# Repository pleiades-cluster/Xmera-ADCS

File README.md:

# Xmera-ADCS
The Official ADCS Design on PROVES Xmera
# ADCS_V1
This was the first version of the ADCS board developed by Rachel Sarmiento and Nicole Maggard. This board was uploaded on 10/12/2022 and is the most relevant and up to date version. This board utilizes a raspberry pi zero for calculations and control. This board includes an embedded Magnetorquer in the inner layers. Parts utilized on V1 include: STSPIN250 (Motor Drivers), PCA9548A (I2C Multiplexer), LIS331LH (6D Orientation IMUs), and LIS3MDL (Magnetometers).

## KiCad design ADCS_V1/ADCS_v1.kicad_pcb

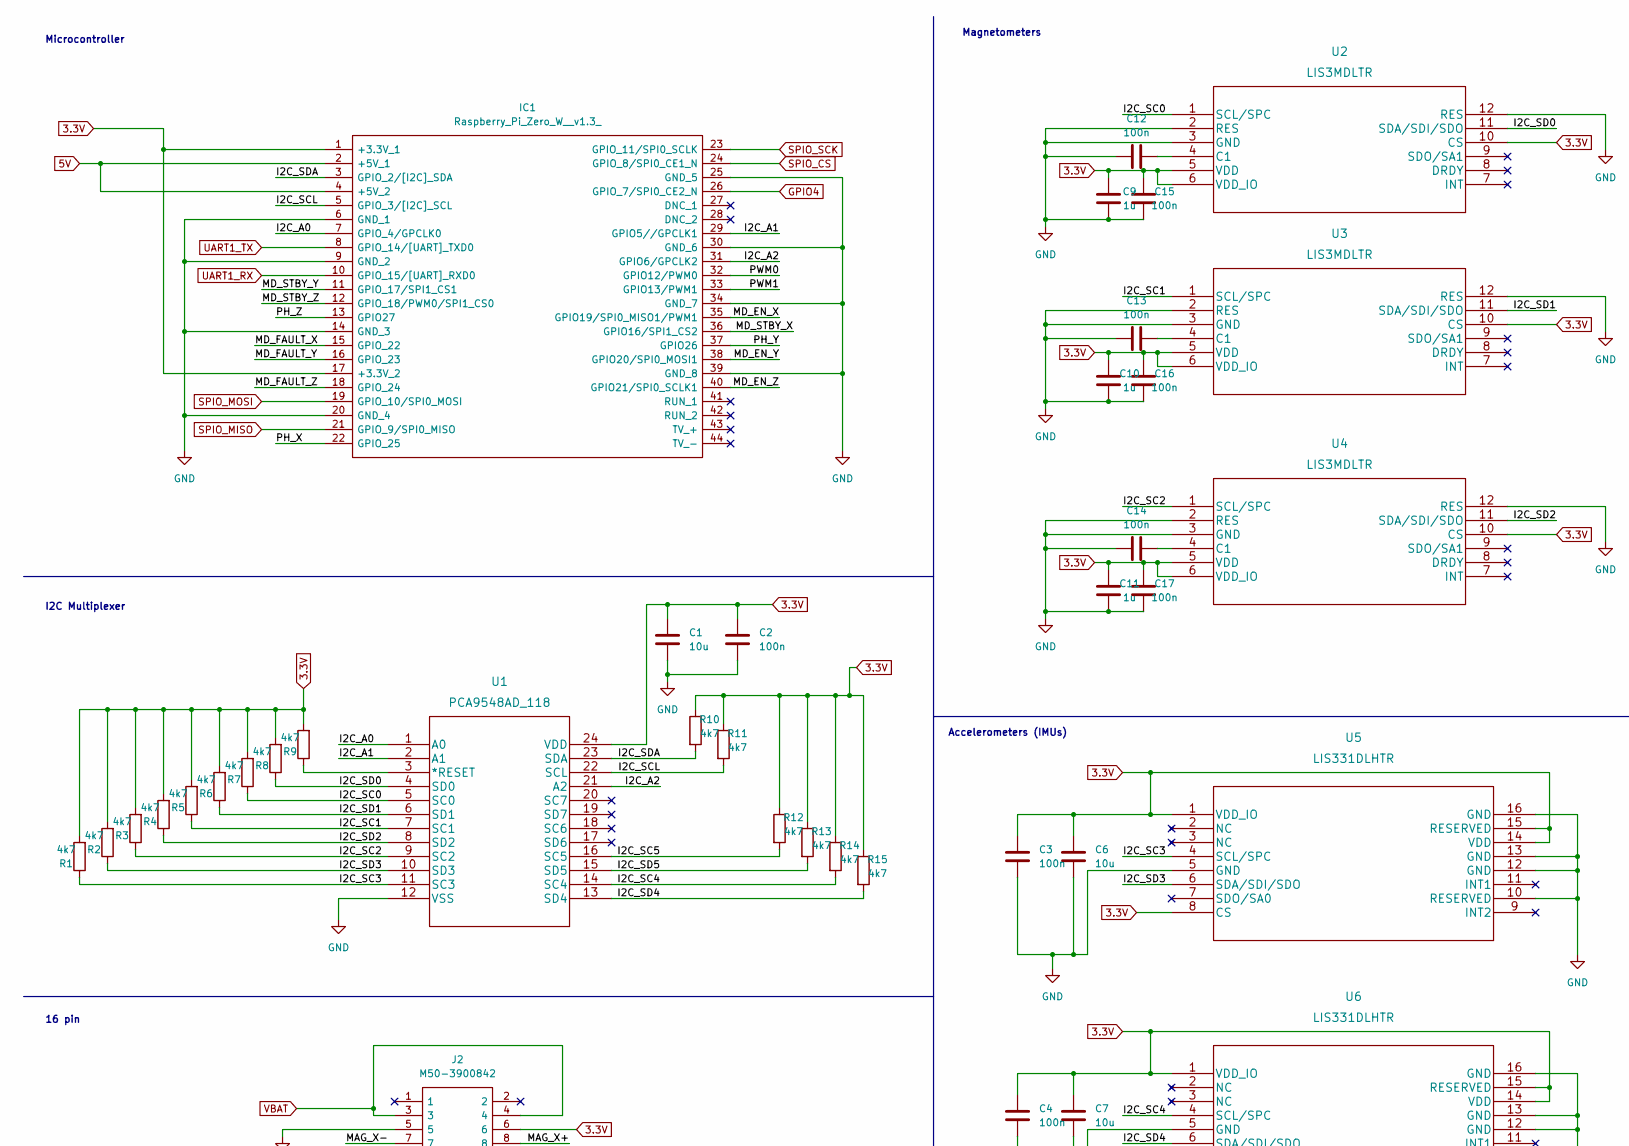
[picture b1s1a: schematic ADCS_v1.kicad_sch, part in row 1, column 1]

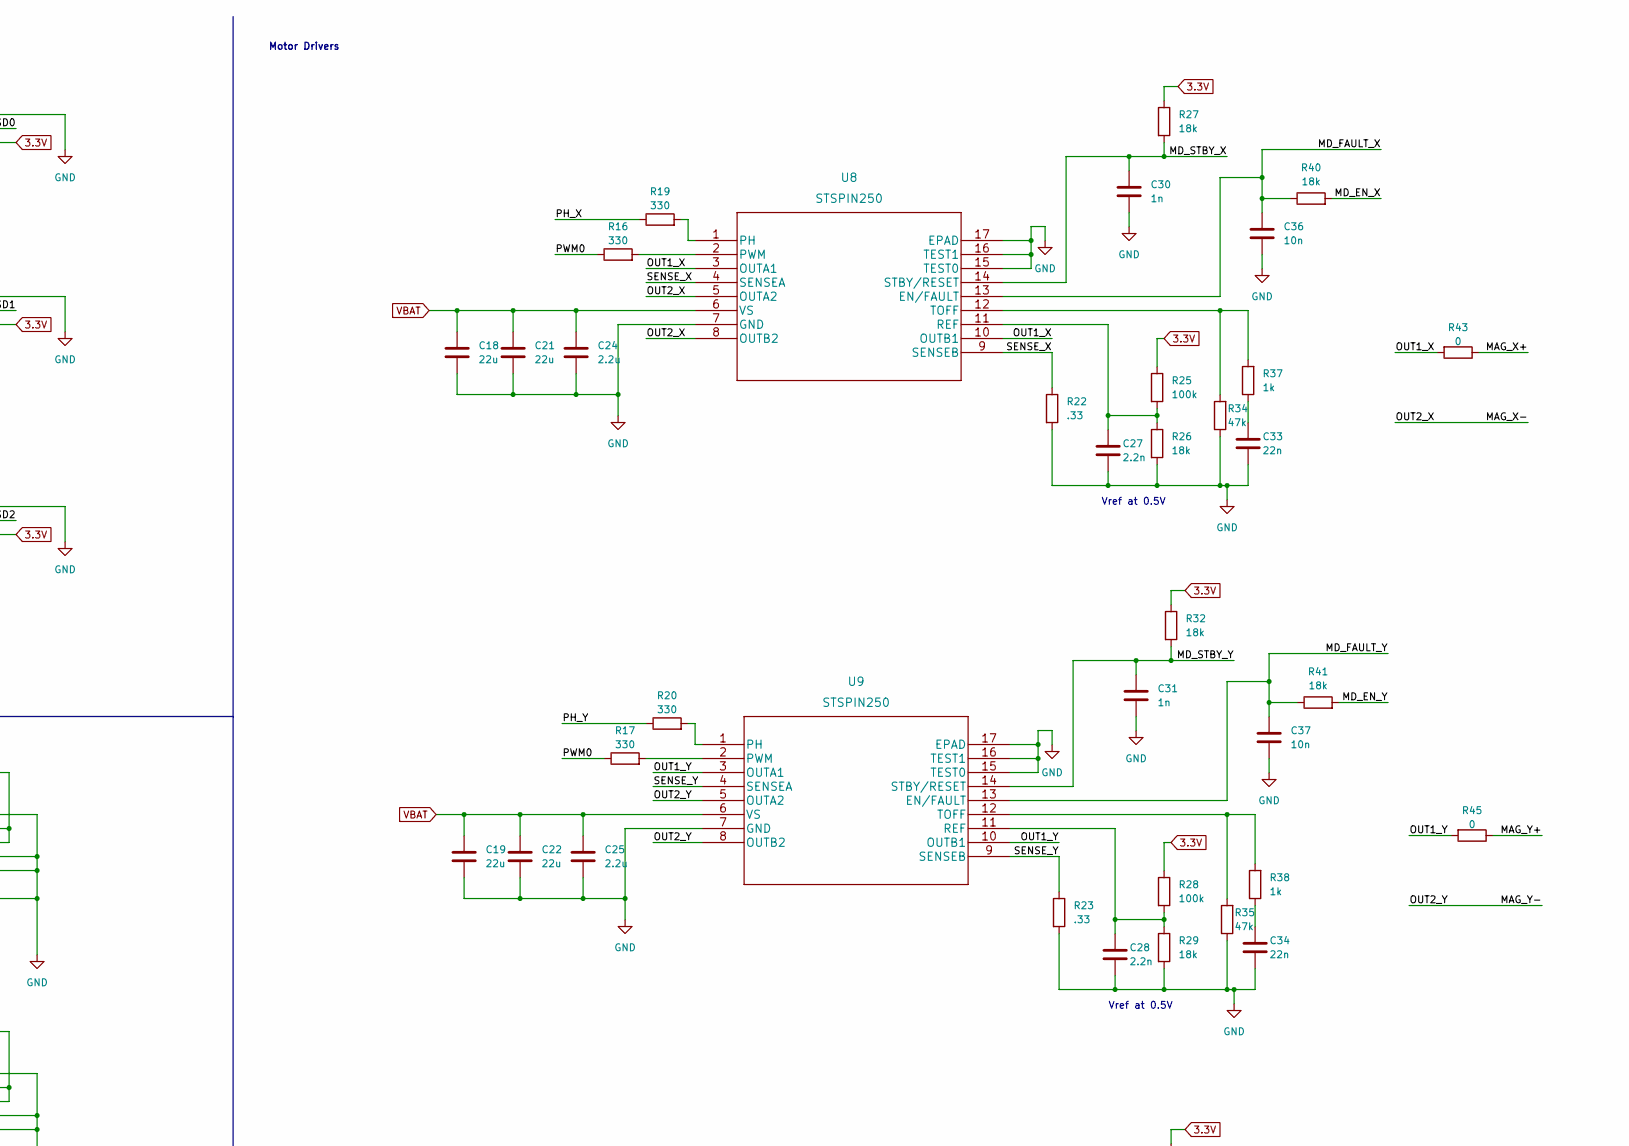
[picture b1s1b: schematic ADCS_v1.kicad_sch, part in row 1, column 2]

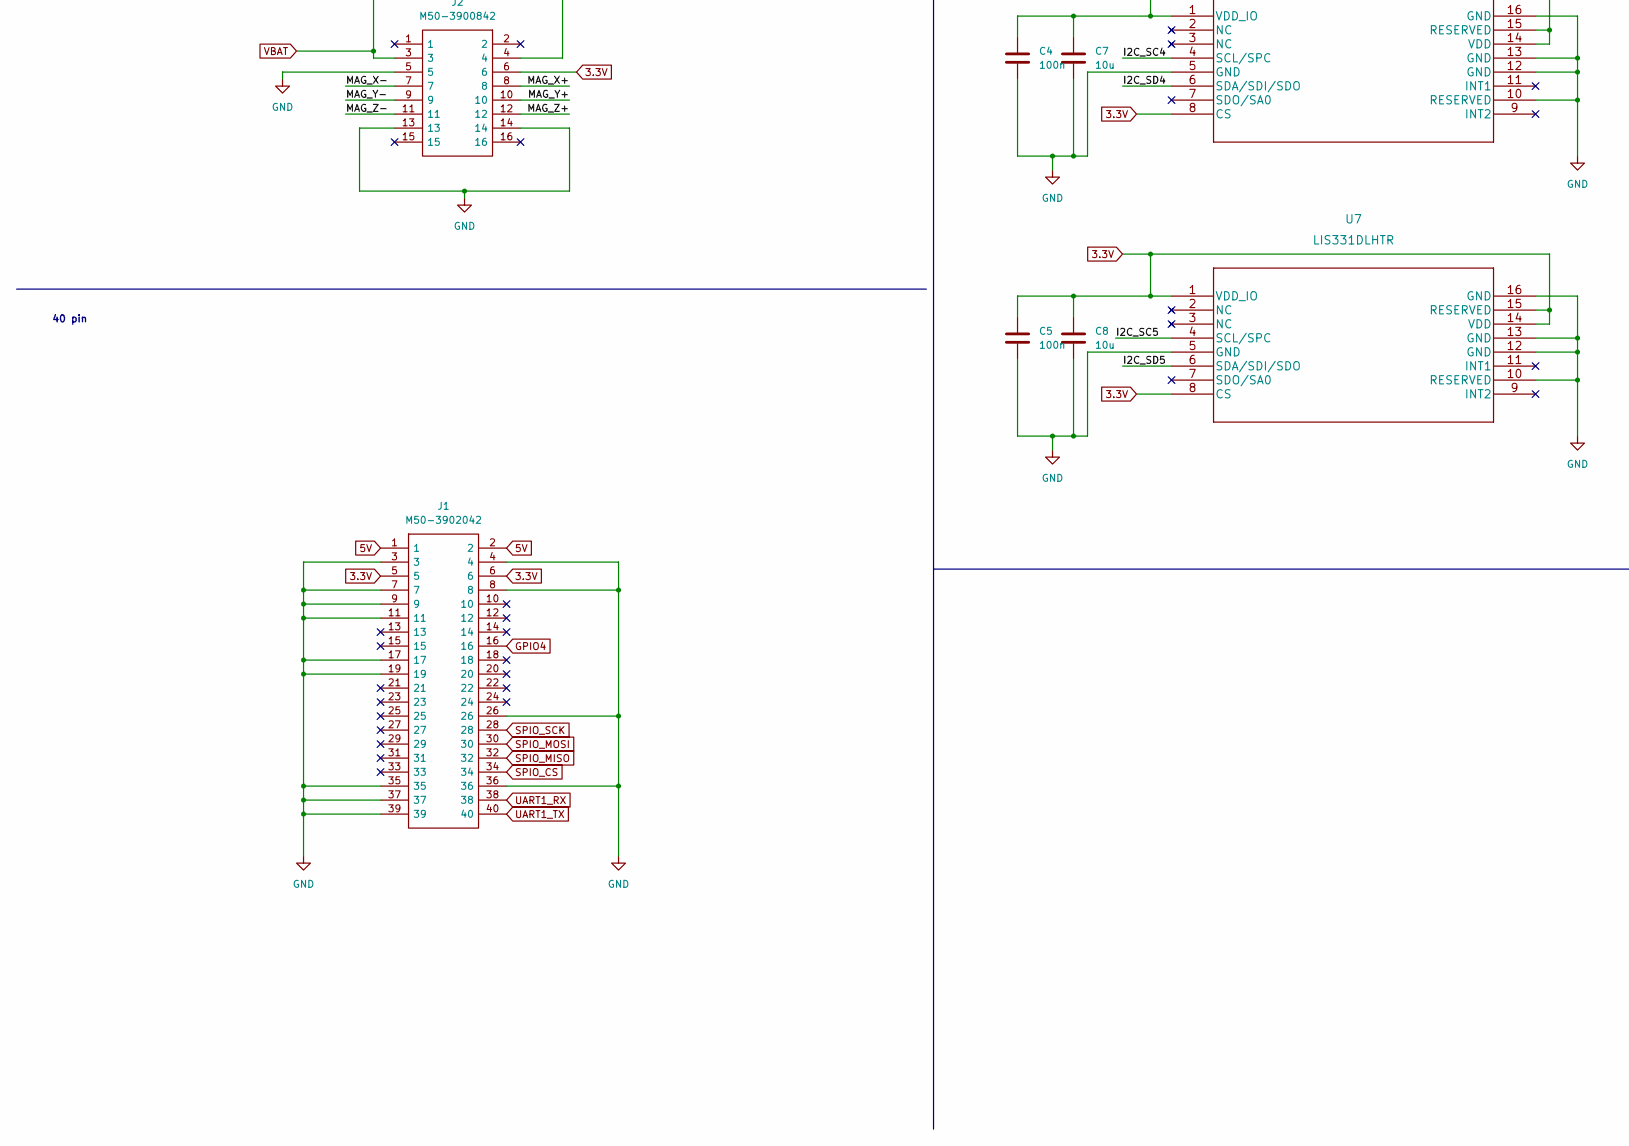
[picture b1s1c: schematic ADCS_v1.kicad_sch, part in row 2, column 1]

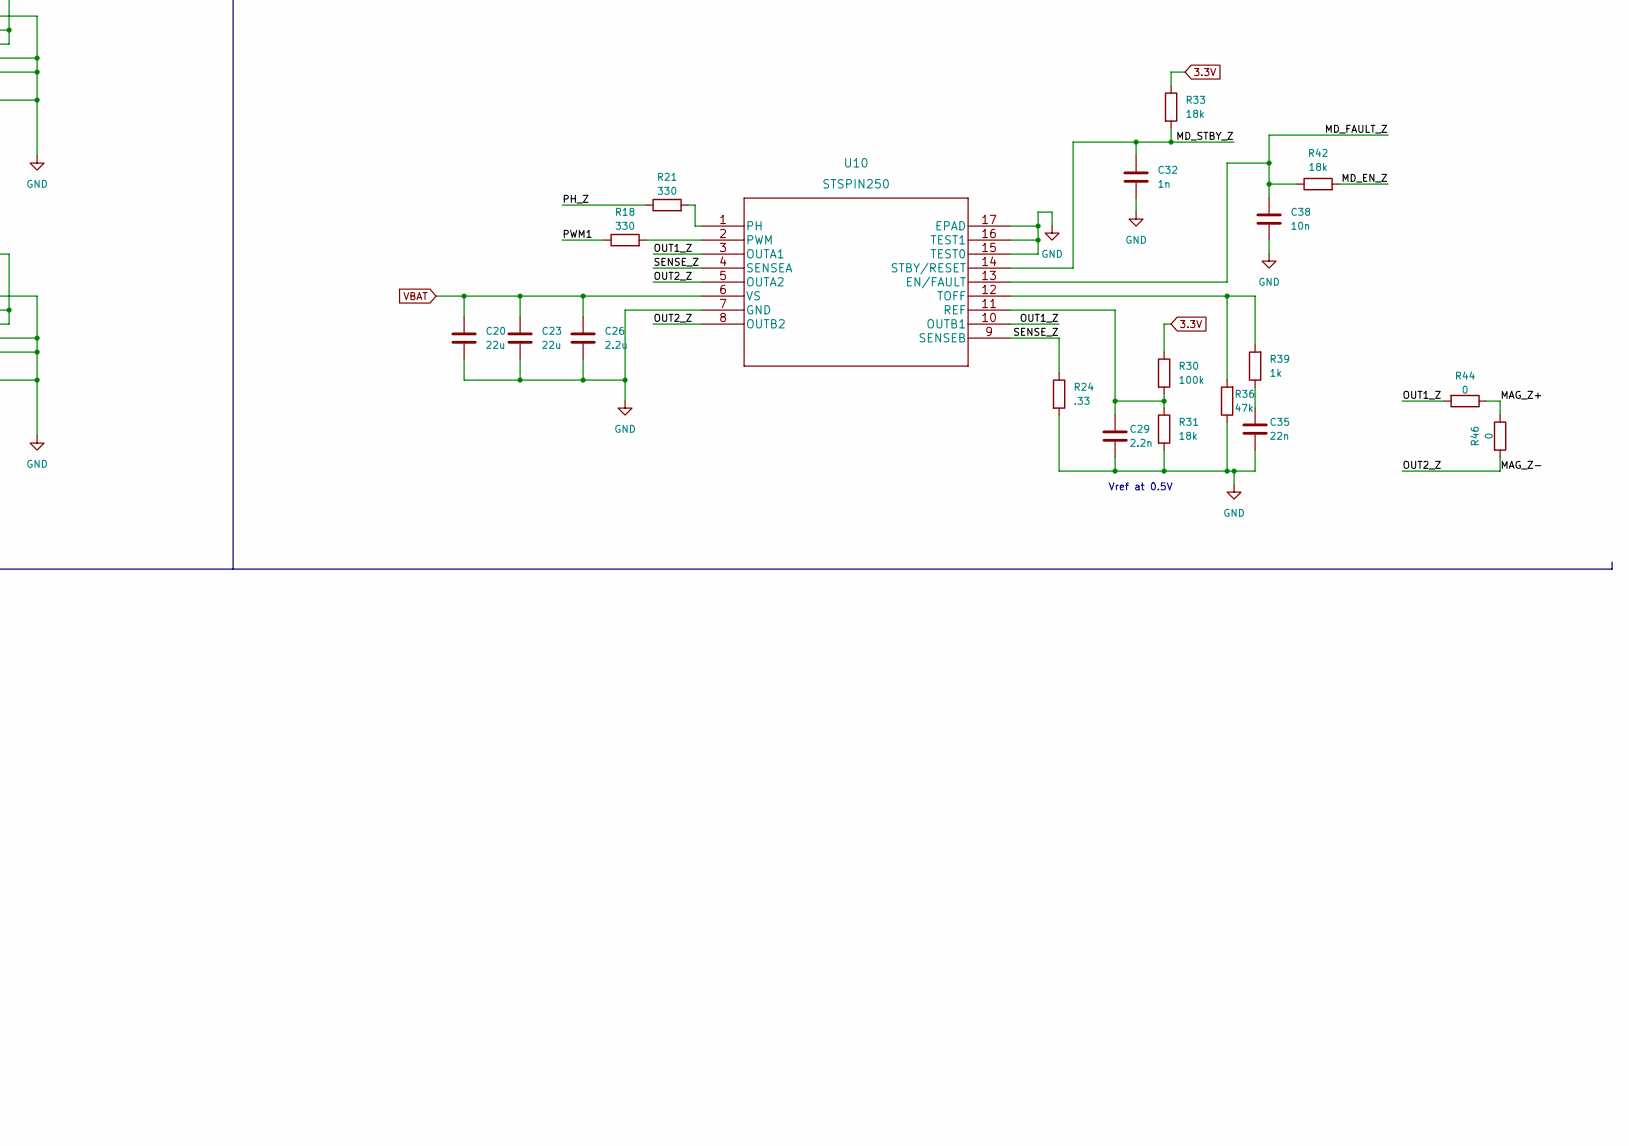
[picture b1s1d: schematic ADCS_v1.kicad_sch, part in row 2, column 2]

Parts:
C1, C6, C7, C8: 10u; C_0603_1608Metric
C2, C3, C4, C5, C12, C13, C14, C15, C16, C17: 100n; C_0402_1005Metric
C9, C10, C11: 1u; C_0402_1005Metric
C18, C19, C20, C21, C22, C23: 22u; C_0805_2012Metric
C24, C25, C26: 2.2u; C_0603_1608Metric
C27, C28, C29: 2.2n; C_0402_1005Metric
C30, C31, C32: 1n; C_0402_1005Metric
C33, C34, C35: 22n; C_0402_1005Metric
C36, C37, C38: 10n; C_0402_1005Metric
IC1: Raspberry_Pi_Zero_W__v1.3_; RASPBERRYPIZEROWV13; Manufacturer_Part_Number Raspberry Pi Zero W (v1.3)
J1: M50-3902042; Mouser Part Number 855-M50-3902042
J2: M50-3900842; Mouser Part Number 855-M50-3900842
R1, R2, R3, R4, R5, R6, R7, R8, R9, R10, R11, R12, R13, R14, R15: 4k7; R_0402_1005Metric
R16, R17, R18, R19, R20, R21: 330; R_0402_1005Metric
R22, R23, R24: .33; R_0402_1005Metric
R25, R28, R30: 100k; R_0805_2012Metric
R26, R27, R29, R31, R32, R33, R40, R41, R42: 18k; R_0603_1608Metric
R34, R35, R36: 47k; R_0805_2012Metric
R37, R38, R39: 1k; R_0402_1005Metric
R43, R44, R45, R46: 0; R_0402_1005Metric
U1: PCA9548AD_118; SO24_SOT137-1_NXP
U2, U3, U4: LIS3MDLTR; LGA-12_2X2X1_STM
U5, U6, U7: LIS331DLHTR; LGA-16_3x3x1mm_STM
U8, U9, U10: STSPIN250; VFQFPN16_STSPIN_STM

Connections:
3.3V: C1.1, C2.1, C3.1, C4.1, C5.1, C6.1, C7.1, C8.1, C9.2, C10.2, C11.2, C15.2, C16.2, C17.2, IC1.1 (+3.3V_1), IC1.17 (+3.3V_2), J1.5, J1.6, J2.6, R1.2, R2.2, R3.2, R4.2, R5.2, R6.2, R7.2, R8.2, R9.2, R10.1, R11.1, R12.1, R13.1, R14.1, R15.1, R25.1, R27.1, R28.1, R30.1, R32.1, R33.1, U1.24 (VDD), U2.5 (VDD), U2.6 (VDD_IO), U2.10 (CS), U3.5 (VDD), U3.6 (VDD_IO), U3.10 (CS), U4.5 (VDD), U4.6 (VDD_IO), U4.10 (CS), U5.1 (VDD_IO), U5.8 (CS), U5.14 (VDD), U5.15 (RESERVED), U6.1 (VDD_IO), U6.8 (CS), U6.14 (VDD), U6.15 (RESERVED), U7.1 (VDD_IO), U7.8 (CS), U7.14 (VDD), U7.15 (RESERVED); also elsewhere on the board
5V: IC1.2 (+5V_1), IC1.4 (+5V_2), J1.1, J1.2
/I2C_A0: IC1.7 (GPIO_4/GPCLK0), U1.1 (A0)
/I2C_A1: IC1.29 (GPIO5//GPCLK1), U1.2 (A1)
/I2C_A2: IC1.31 (GPIO6/GPCLK2), U1.21 (A2); also elsewhere on the board
/I2C_SC0: R7.1, U1.5 (SC0), U2.1 (SCL/SPC)
/I2C_SC1: R5.1, U1.7 (SC1), U3.1 (SCL/SPC)
/I2C_SC2: R3.1, U1.9 (SC2), U4.1 (SCL/SPC)
/I2C_SC3: R1.1, U1.11 (SC3), U5.4 (SCL/SPC)
/I2C_SC4: R14.2, U1.14 (SC4), U6.4 (SCL/SPC)
/I2C_SC5: R12.2, U1.16 (SC5), U7.4 (SCL/SPC)
/I2C_SCL: IC1.5 (GPIO_3/[I2C]_SCL), R11.2, U1.22 (SCL)
/I2C_SD0: R8.1, U1.4 (SD0), U2.11 (SDA/SDI/SDO)
/I2C_SD1: R6.1, U1.6 (SD1), U3.11 (SDA/SDI/SDO)
/I2C_SD2: R4.1, U1.8 (SD2), U4.11 (SDA/SDI/SDO)
/I2C_SD3: R2.1, U1.10 (SD3), U5.6 (SDA/SDI/SDO)
/I2C_SD4: R15.2, U1.13 (SD4), U6.6 (SDA/SDI/SDO)
/I2C_SD5: R13.2, U1.15 (SD5), U7.6 (SDA/SDI/SDO)
/I2C_SDA: IC1.3 (GPIO_2/[I2C]_SDA), R10.2, U1.23 (SDA)
/MAG_X+: J2.8, R43.1
/MAG_X-: J2.7, U8.5 (OUTA2), U8.8 (OUTB2)
/MAG_Y+: J2.10, R45.1
/MAG_Y-: J2.9, U9.5 (OUTA2), U9.8 (OUTB2)
/MAG_Z+: J2.12, R44.1, R46.1
/MAG_Z-: J2.11, R46.2, U10.5 (OUTA2), U10.8 (OUTB2)
/MD_EN_X: IC1.35 (GPIO19/SPI0_MISO1/PWM1), R40.2
/MD_EN_Y: IC1.38 (GPIO20/SPI0_MOSI1), R41.2
/MD_EN_Z: IC1.40 (GPIO21/SPI0_SCLK1), R42.2
/MD_FAULT_X: C36.1, IC1.15 (GPIO_22), R40.1, U8.13 (EN/FAULT)
/MD_FAULT_Y: C37.1, IC1.16 (GPIO_23), R41.1, U9.13 (EN/FAULT)
/MD_FAULT_Z: C38.1, IC1.18 (GPIO_24), R42.1, U10.13 (EN/FAULT)
/MD_STBY_X: C30.1, IC1.36 (GPIO16/SPI1_CS2), R27.2, U8.14 (STBY/RESET)
/MD_STBY_Y: C31.1, IC1.11 (GPIO_17/SPI1_CS1), R32.2, U9.14 (STBY/RESET)
/MD_STBY_Z: C32.1, IC1.12 (GPIO_18/PWM0/SPI1_CS0), R33.2, U10.14 (STBY/RESET)
/OUT1_X: R43.2, U8.3 (OUTA1), U8.10 (OUTB1)
/OUT1_Y: R45.2, U9.3 (OUTA1), U9.10 (OUTB1)
/OUT1_Z: R44.2, U10.3 (OUTA1), U10.10 (OUTB1)
/PH_X: IC1.22 (GPIO_25), R19.1
/PH_Y: IC1.37 (GPIO26), R20.1
/PH_Z: IC1.13 (GPIO27), R21.1
/PWM0: IC1.32 (GPIO12/PWM0), R16.1, R17.1
/PWM1: IC1.33 (GPIO13/PWM1), R18.1
/SENSE_X: R22.1, U8.4 (SENSEA), U8.9 (SENSEB)
/SENSE_Y: R23.1, U9.4 (SENSEA), U9.9 (SENSEB)
/SENSE_Z: R24.1, U10.4 (SENSEA), U10.9 (SENSEB)
GND: C1.2, C2.2, C3.2, C4.2, C5.2, C6.2, C7.2, C8.2, C9.1, C10.1, C11.1, C12.1, C13.1, C14.1, C15.1, C16.1, C17.1, C18.2, C19.2, C20.2, C21.2, C22.2, C23.2, C24.2, C25.2, C26.2, C27.2, C28.2, C29.2, C30.2, C31.2, C32.2, C33.2, C34.2, C35.2, C36.2, C37.2, C38.2, IC1.6 (GND_1), IC1.9 (GND_2), IC1.14 (GND_3), IC1.20 (GND_4), IC1.25 (GND_5), IC1.30 (GND_6), IC1.34 (GND_7), IC1.39 (GND_8), J1.3, J1.4, J1.7, J1.8, J1.9, J1.11, J1.17, J1.19, J1.26, J1.35, J1.36, J1.37, J1.39, J2.5, J2.13, J2.14, R22.2, R23.2, R24.2, R26.2, R29.2, R31.2, R34.1, R35.1, R36.1, U1.12 (VSS), U2.2 (RES), U2.3 (GND), U2.12 (RES), U3.2 (RES), U3.3 (GND), U3.12 (RES), U4.2 (RES), U4.3 (GND), U4.12 (RES), U5.5 (GND), U5.10 (RESERVED), U5.12 (GND), U5.13 (GND), U5.16 (GND), U6.5 (GND), U6.10 (RESERVED), U6.12 (GND), U6.13 (GND), U6.16 (GND), U7.5 (GND), U7.10 (RESERVED), U7.12 (GND), U7.13 (GND), U7.16 (GND), U8.7 (GND), U8.15 (TEST0), U8.16 (TEST1), U8.17 (EPAD), U9.7 (GND), U9.15 (TEST0), U9.16 (TEST1), U9.17 (EPAD), U10.7 (GND), U10.15 (TEST0), U10.16 (TEST1), U10.17 (EPAD)
GPIO4: IC1.26 (GPIO_7/SPI0_CE2_N), J1.16
unnamed: C12.2, U2.4 (C1)
unnamed: C13.2, U3.4 (C1)
unnamed: C14.2, U4.4 (C1)
unnamed: C27.1, R25.2, R26.1, U8.11 (REF)
unnamed: C28.1, R28.2, R29.1, U9.11 (REF)
unnamed: C29.1, R30.2, R31.1, U10.11 (REF)
unnamed: C33.1, R37.1
unnamed: C34.1, R38.1
unnamed: C35.1, R39.1
unnamed: R9.1, U1.3 (*RESET)
unnamed: R16.2, U8.2 (PWM)
unnamed: R17.2, U9.2 (PWM)
unnamed: R18.2, U10.2 (PWM)
unnamed: R19.2, U8.1 (PH)
unnamed: R20.2, U9.1 (PH)
unnamed: R21.2, U10.1 (PH)
unnamed: R34.2, R37.2, U8.12 (TOFF)
unnamed: R35.2, R38.2, U9.12 (TOFF)
unnamed: R36.2, R39.2, U10.12 (TOFF)
SPIO_CS: IC1.24 (GPIO_8/SPI0_CE1_N), J1.34
SPIO_MISO: IC1.21 (GPIO_9/SPI0_MISO), J1.32
SPIO_MOSI: IC1.19 (GPIO_10/SPI0_MOSI), J1.30
SPIO_SCK: IC1.23 (GPIO_11/SPI0_SCLK), J1.28
UART1_RX: IC1.10 (GPIO_15/[UART]_RXD0), J1.38
UART1_TX: IC1.8 (GPIO_14/[UART]_TXD0), J1.40
VBAT: C18.1, C19.1, C20.1, C21.1, C22.1, C23.1, C24.1, C25.1, C26.1, J2.3, J2.4, U8.6 (VS), U9.6 (VS), U10.6 (VS)

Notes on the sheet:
Motor Drivers
Vref at 0.5V
16 pin
Magnetometers
40 pin
I2C Multiplexer
Microcontroller
Accelerometers (IMUs)

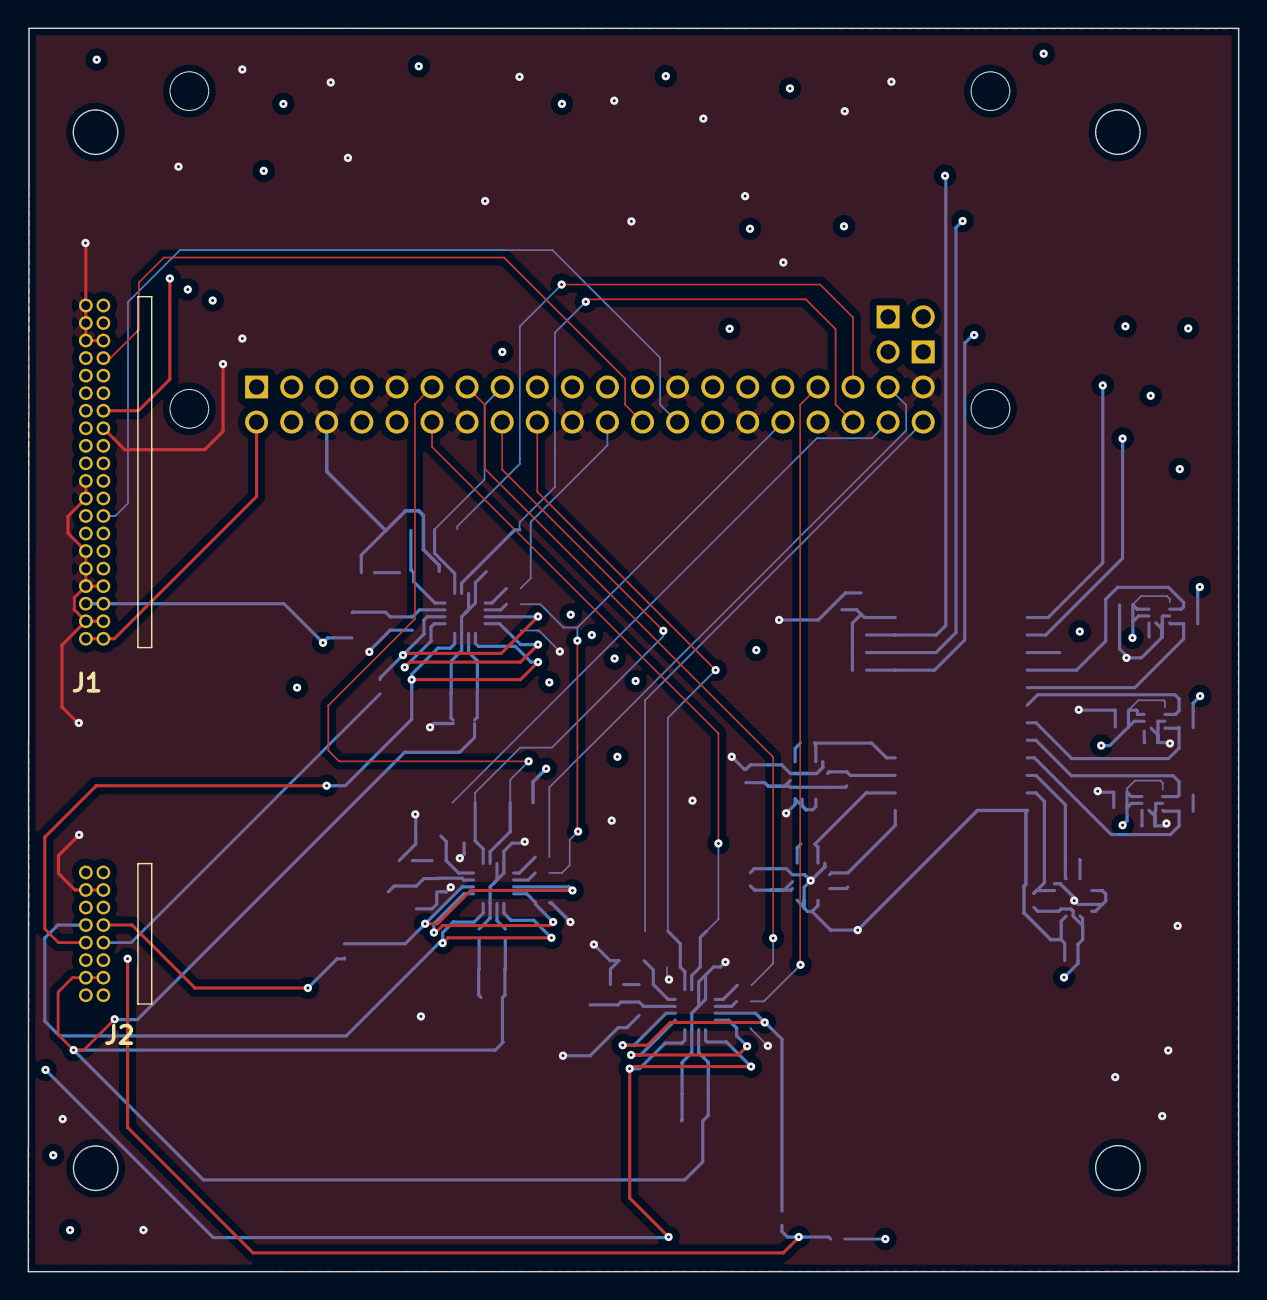
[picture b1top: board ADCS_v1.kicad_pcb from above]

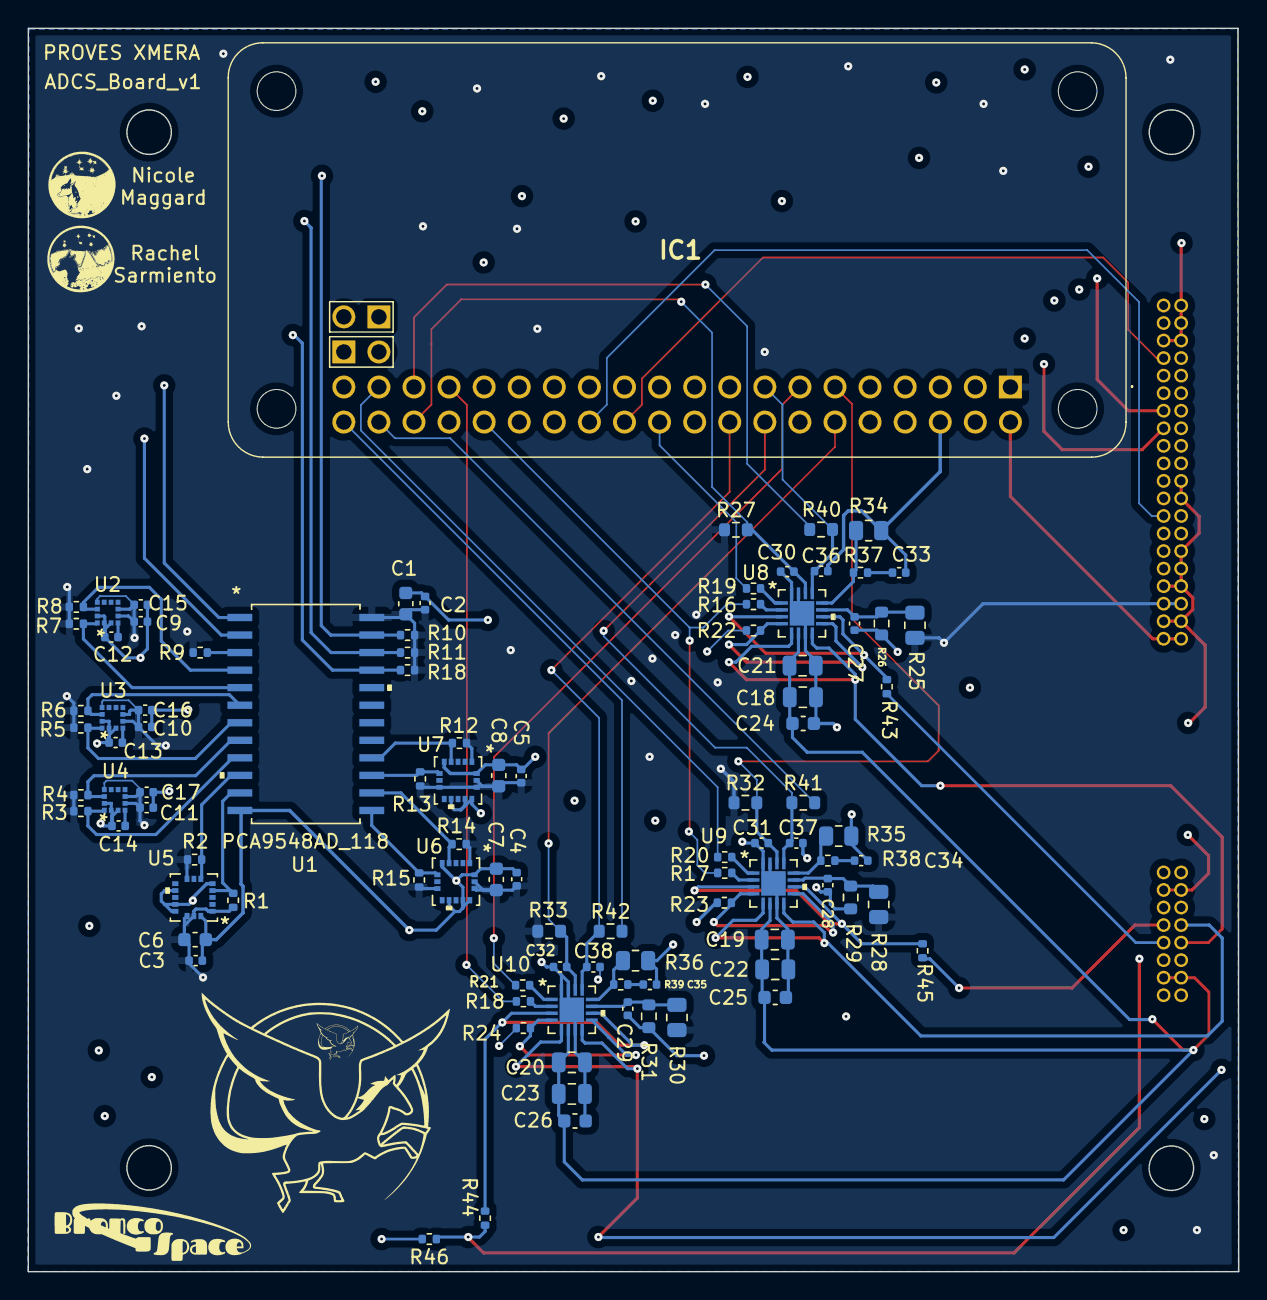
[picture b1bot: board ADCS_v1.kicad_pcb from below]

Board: 4 copper layers, 87.6 x 90.0 mm, 98 parts (96 on the bottom side), 73 nets.

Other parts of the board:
R18#2: 4k7; R_0402_1005Metric

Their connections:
3.3V: R18#2.1; also elsewhere on the board
/I2C_A2: R18#2.2; also elsewhere on the board

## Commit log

2022-10-12 The first version of ADCS
2022-10-16 40 pin and 16 pin def update
2022-10-30 changed connector positions
2022-10-31 updated 3d models (.step and .wrl)
2022-10-31 updated connectors and 3dmodels

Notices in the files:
parts and their libraries:
Copyright 2021 Accelerated Designs. All rights reserved.
